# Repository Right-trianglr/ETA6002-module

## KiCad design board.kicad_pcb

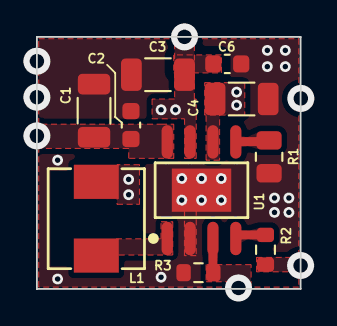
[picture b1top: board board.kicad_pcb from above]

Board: 2 copper layers, 14.6 x 14.0 mm, 10 parts (0 on the bottom side), 8 nets.

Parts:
C1, C3, C4: 22uF X7R 10V; C_1206_3216Metric
C2, C6: 100nF X7R 10V; C_0603_1608Metric
L1: 2.2uH 7A ±20%; IND-SMD_L5.4-W5.2
R1: 500ohm ±1%; R_0805_2012Metric
R2: 2.2K; R_0603_1608Metric
R3: 0ohm; R_0603_1608Metric
U1: ETA6002; ESOP-8_L4.9-W3.9-P1.27-LS6.0-BL-EP-1

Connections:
BAT: C4.1, U1.6 (BATT)
GND: C1.2, C2.2, C3.2, C4.2, C6.2, R1.2, R3.1, U1.2 (PGND), U1.9 (EP)
NTC: R3.2, U1.3 (NTC)
unnamed: R1.1, U1.5 (ISET)
unnamed: R2.2, U1.4 (STAT)
unnamed: L1.1, U1.1 (SW)
VIN: C1.1, C2.1, U1.8 (IN)
VOUT: C3.1, C6.1, L1.2, U1.7 (SYS)

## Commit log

2025-11-23 上传电路初版
2025-11-23 添加原理图
